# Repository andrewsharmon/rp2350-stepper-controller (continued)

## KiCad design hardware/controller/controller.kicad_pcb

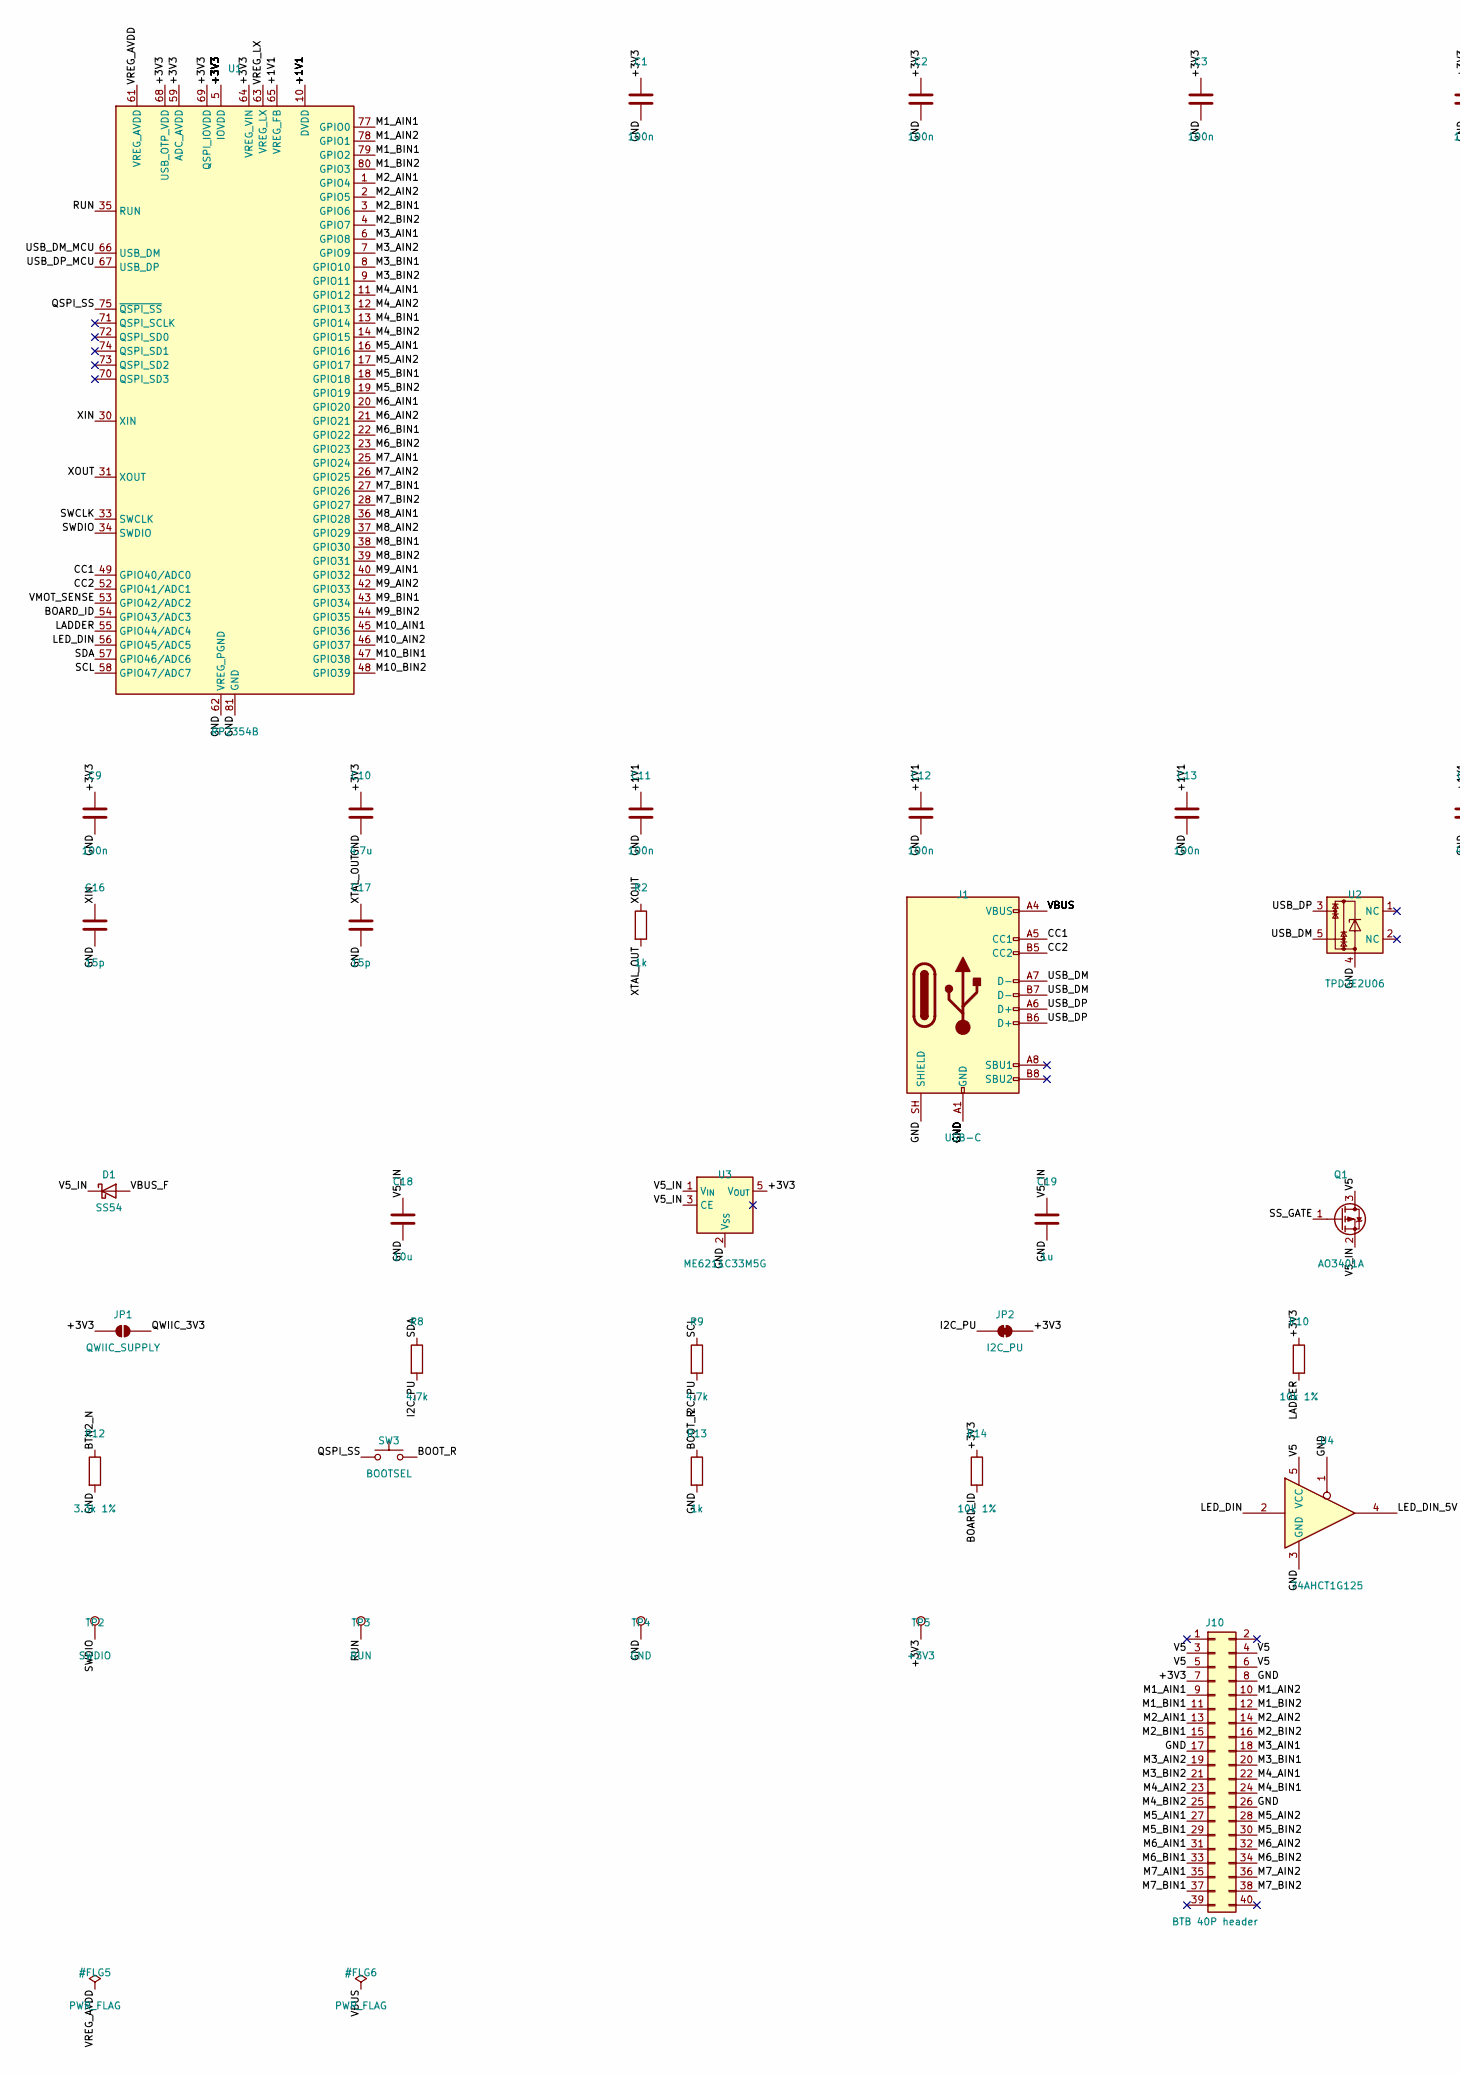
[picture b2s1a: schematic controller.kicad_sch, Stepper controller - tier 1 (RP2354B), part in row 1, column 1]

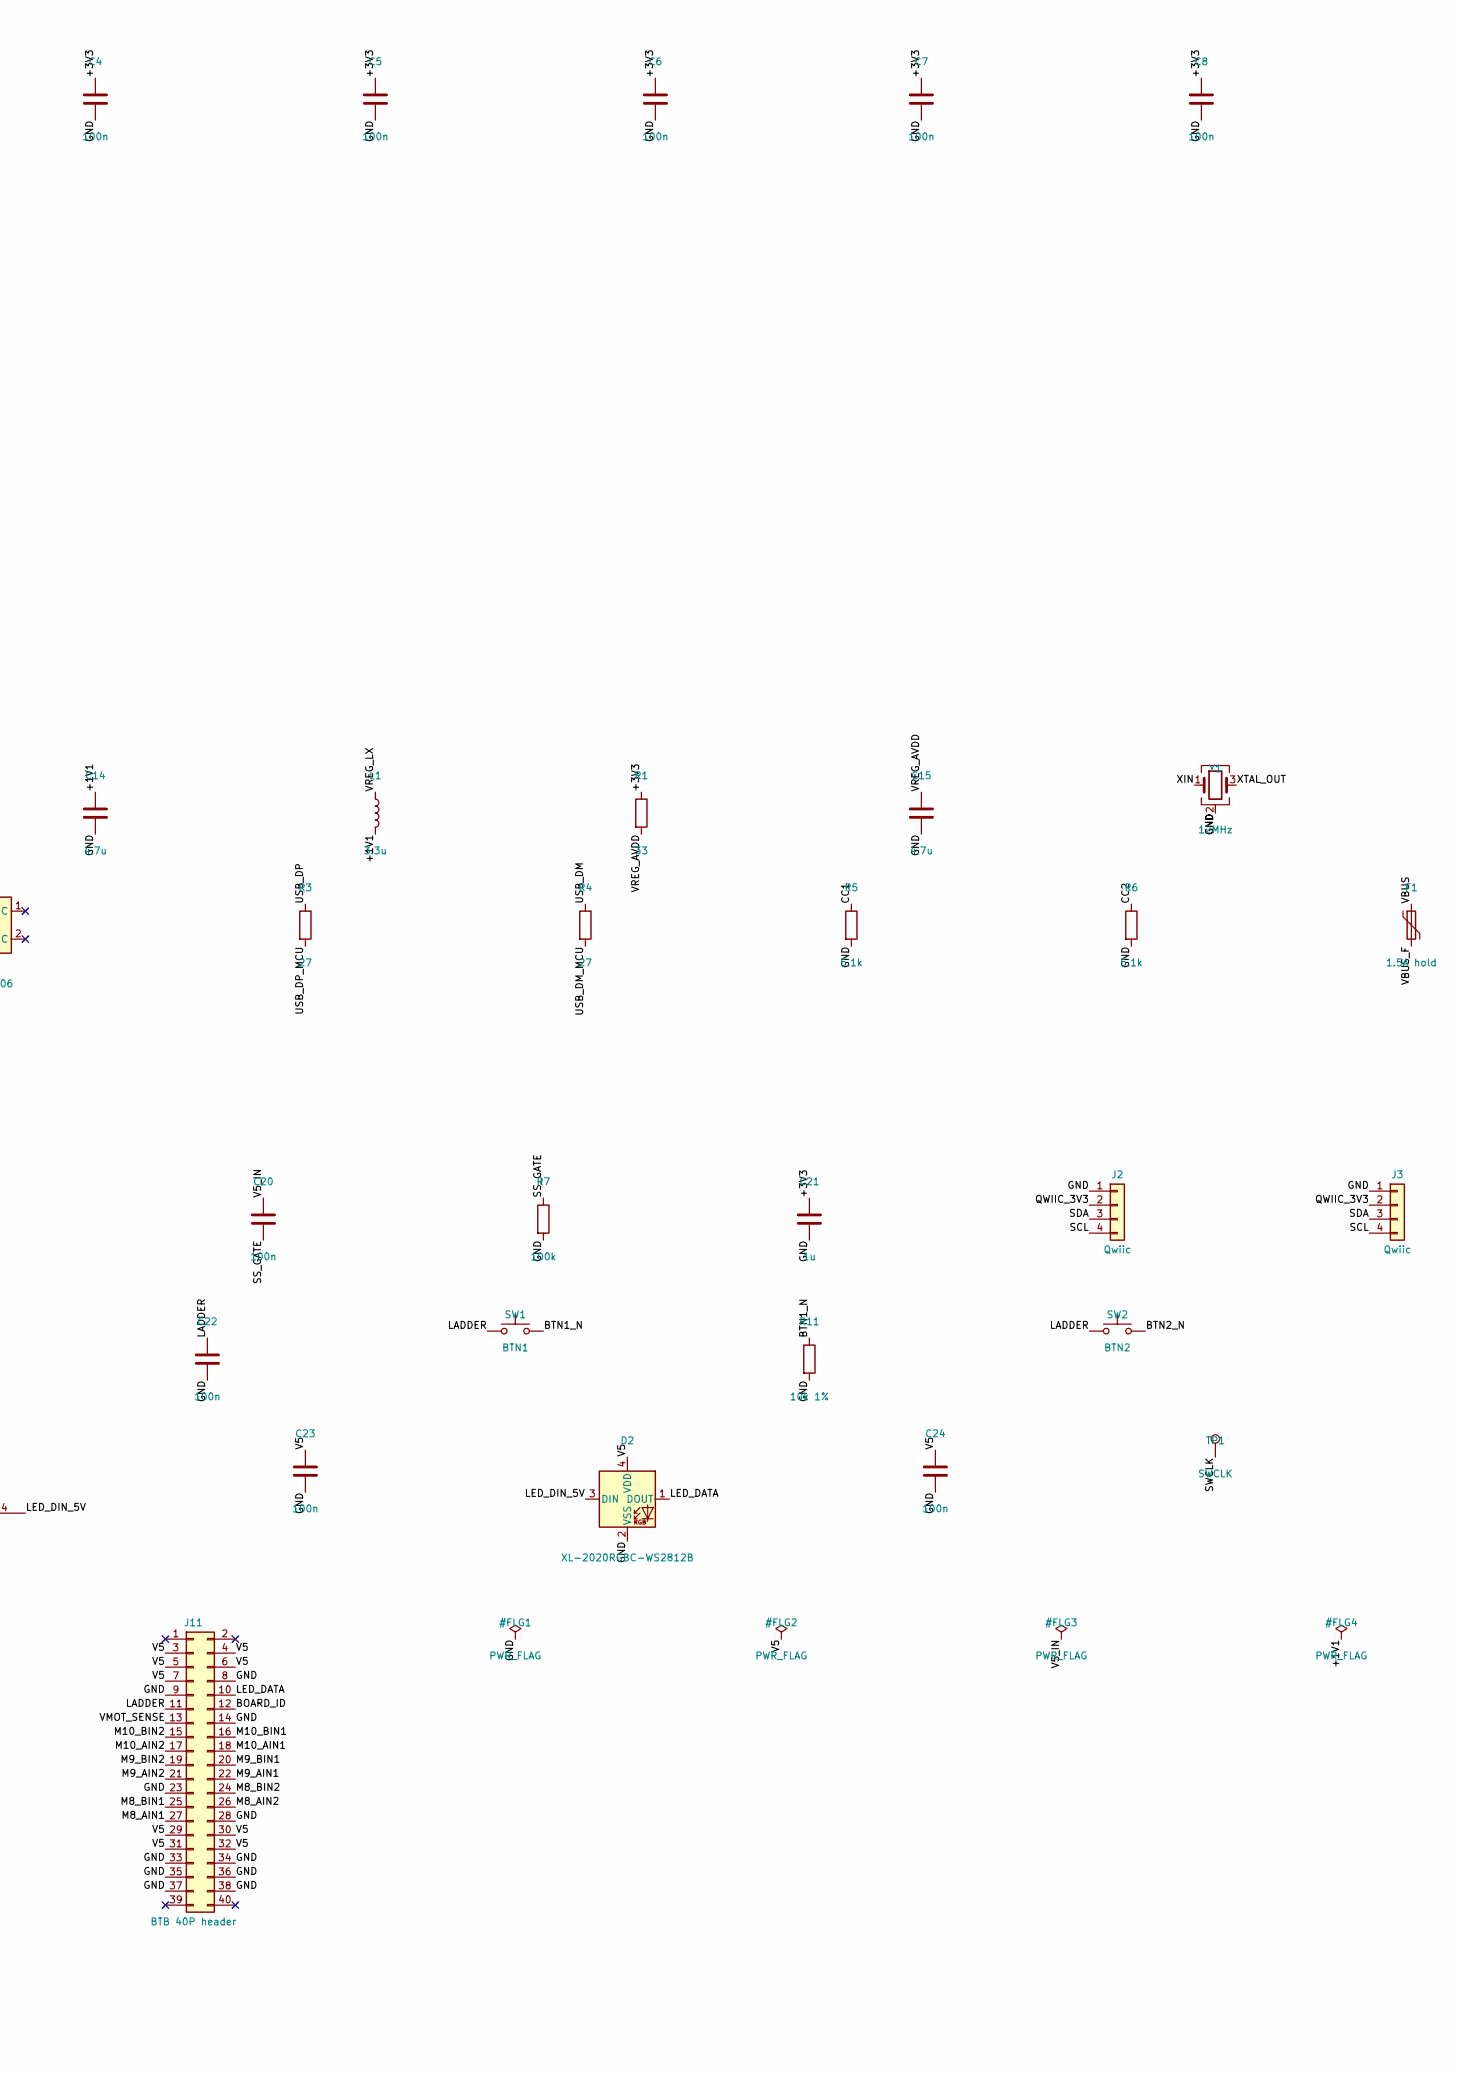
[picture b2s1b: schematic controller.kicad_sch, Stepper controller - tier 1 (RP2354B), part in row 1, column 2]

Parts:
C1, C2, C3, C4, C5, C6, C7, C8, C9, C11, C12, C13, C20, C22, C23, C24: 100n; C_0402_1005Metric; MPN CL05B104KO5NNNC; LCSC C1525
C10, C14, C15: 4.7u; C_0402_1005Metric; MPN CL05A475MP5NRNC; LCSC C23733
C16, C17: 15p; C_0402_1005Metric; MPN 0402CG150J500NT; LCSC C1548
C18: 10u; C_0805_2012Metric; MPN CL21A106KAYNNNE; LCSC C15850
C19, C21: 1u; C_0402_1005Metric; MPN CL05A105KA5NQNC; LCSC C52923
D1: SS54; D_SMA; MPN SS54; LCSC C22452
D2: XL-2020RGBC-WS2812B; LED_WS2812B-2020_PLCC4_2.0x2.0mm; MPN XL-2020RGBC-WS2812B; LCSC C5349955
F1: 1.5A hold; Fuse_1812_4532Metric; MPN SMD1812P150TF/8; LCSC C209721
J1: USB-C; USB_C_Receptacle_HRO_TYPE-C-31-M-12; MPN TYPE-C-31-M-12; LCSC C165948
J2, J3: Qwiic; JST_SH_BM04B-SRSS-TB_1x04-1MP_P1.00mm_Vertical; MPN BM04B-SRSS-TB; LCSC C160390
J10, J11: BTB 40P header; Hirose_DF40C-40DP_Header; MPN DF40C-40DP-0.4V(51); LCSC C424643
JP1: QWIIC_SUPPLY; SolderJumper-2_P1.3mm_Open_RoundedPad1.0x1.5mm
JP2: I2C_PU; SolderJumper-2_P1.3mm_Bridged_RoundedPad1.0x1.5mm
L1: 3.3u; L_Cenker_CKCS201610; MPN AOTA-B201610S3R3-101-T; LCSC C42411119
Q1: AO3401A; SOT-23; MPN AO3401A; LCSC C15127
R1: 33; R_0402_1005Metric; MPN 0402WGF330JTCE; LCSC C25105
R2, R13: 1k; R_0402_1005Metric; MPN 0402WGF1001TCE; LCSC C11702
R3, R4: 27; R_0402_1005Metric; MPN 0402WGF270JTCE; LCSC C25100
R5, R6: 5.1k; R_0402_1005Metric; MPN 0402WGF5101TCE; LCSC C25905
R7: 100k; R_0402_1005Metric; MPN 0402WGF1003TCE; LCSC C25741
R8, R9: 4.7k; R_0402_1005Metric; MPN 0402WGF4701TCE; LCSC C25900
R10, R11, R14: 10k 1%; R_0402_1005Metric; MPN 0402WGF1002TCE; LCSC C25744
R12: 3.3k 1%; R_0402_1005Metric; MPN 0402WGF3301TCE; LCSC C25890
SW1: BTN1; SW_SPST_TS-1088-xR020; MPN TS-1088-AR02016; LCSC C720477
SW2: BTN2; SW_SPST_TS-1088-xR020; MPN TS-1088-AR02016; LCSC C720477
SW3: BOOTSEL; SW_Push_1P1T_XKB_TS-1187A; MPN TS-1187A-B-A-B; LCSC C318884
TP1: SWCLK; TestPoint_Pad_D1.0mm
TP2: SWDIO; TestPoint_Pad_D1.0mm
TP3: RUN; TestPoint_Pad_D1.0mm
TP4: GND; TestPoint_Pad_D1.0mm
TP5: +3V3; TestPoint_Pad_D1.0mm
U1: RP2354B; QFN-80-1EP_10x10mm_P0.4mm_EP3.4x3.4mm; MPN RP2354B; LCSC C39843328
U2: TPD2E2U06; SOT-553; MPN TPD2E2U06DRLR; LCSC C1972959
U3: ME6211C33M5G; SOT-23-5; MPN ME6211C33M5G-N; LCSC C82942
U4: 74AHCT1G125; SOT-23-5; MPN SN74AHCT1G125DBVR; LCSC C7484
Y1: 12MHz; Crystal_SMD_3225-4Pin_3.2x2.5mm; MPN ABM8-272-T3; LCSC C20625731

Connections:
/+1V1: C11.1, C12.1, C13.1, C14.1, L1.2, U1.10 (DVDD), U1.32 (DVDD), U1.51 (DVDD), U1.65 (VREG_FB)
/+3V3: C1.1, C2.1, C3.1, C4.1, C5.1, C6.1, C7.1, C8.1, C9.1, C10.1, C21.1, J10.7, JP1.1 (A), JP2.2 (B), R1.1, R10.1, R14.1, TP5.1, U1.5 (IOVDD), U1.15 (IOVDD), U1.24 (IOVDD), U1.29 (IOVDD), U1.41 (IOVDD), U1.50 (IOVDD), U1.59 (ADC_AVDD), U1.60 (IOVDD), U1.64 (VREG_VIN), U1.68 (USB_OTP_VDD), U1.69 (QSPI_IOVDD), U1.76 (IOVDD), U3.5 (V_{OUT})
/BOARD_ID: J11.12, R14.2, U1.54 (GPIO43/ADC3)
/BOOT_R: R13.1, SW3.2
/BTN1_N: R11.1, SW1.2
/BTN2_N: R12.1, SW2.2
/CC1: J1.A5 (CC1), R5.1, U1.49 (GPIO40/ADC0)
/CC2: J1.B5 (CC2), R6.1, U1.52 (GPIO41/ADC1)
/GND: C1.2, C2.2, C3.2, C4.2, C5.2, C6.2, C7.2, C8.2, C9.2, C10.2, C11.2, C12.2, C13.2, C14.2, C15.2, C16.2, C17.2, C18.2, C19.2, C21.2, C22.2, C23.2, C24.2, D2.2 (VSS), J1.A1 (GND), J1.A12 (GND), J1.B1 (GND), J1.B12 (GND), J1.SH (SHIELD), J2.1, J3.1, J10.8, J10.17, J10.26, J11.8, J11.9, J11.14, J11.23, J11.28, J11.33, J11.34, J11.35, J11.36, J11.37, J11.38, R5.2, R6.2, R7.2, R11.2, R12.2, R13.2, TP4.1, U1.62 (VREG_PGND), U1.81 (GND), U2.4, U3.2 (V_{SS}), U4.1, U4.3 (GND), Y1.2 (G), Y1.4 (G)
/I2C_PU: JP2.1 (A), R8.2, R9.2
/LADDER: C22.1, J11.11, R10.2, SW1.1, SW2.1, U1.55 (GPIO44/ADC4)
/LED_DATA: D2.1 (DOUT), J11.10
/LED_DIN: U1.56 (GPIO45/ADC5), U4.2
/LED_DIN_5V: D2.3 (DIN), U4.4
/M1_AIN1: J10.9, U1.77 (GPIO0)
/M1_AIN2: J10.10, U1.78 (GPIO1)
/M1_BIN1: J10.11, U1.79 (GPIO2)
/M1_BIN2: J10.12, U1.80 (GPIO3)
/M2_AIN1: J10.13, U1.1 (GPIO4)
/M2_AIN2: J10.14, U1.2 (GPIO5)
/M2_BIN1: J10.15, U1.3 (GPIO6)
/M2_BIN2: J10.16, U1.4 (GPIO7)
/M3_AIN1: J10.18, U1.6 (GPIO8)
/M3_AIN2: J10.19, U1.7 (GPIO9)
/M3_BIN1: J10.20, U1.8 (GPIO10)
/M3_BIN2: J10.21, U1.9 (GPIO11)
/M4_AIN1: J10.22, U1.11 (GPIO12)
/M4_AIN2: J10.23, U1.12 (GPIO13)
/M4_BIN1: J10.24, U1.13 (GPIO14)
/M4_BIN2: J10.25, U1.14 (GPIO15)
/M5_AIN1: J10.27, U1.16 (GPIO16)
/M5_AIN2: J10.28, U1.17 (GPIO17)
/M5_BIN1: J10.29, U1.18 (GPIO18)
/M5_BIN2: J10.30, U1.19 (GPIO19)
/M6_AIN1: J10.31, U1.20 (GPIO20)
/M6_AIN2: J10.32, U1.21 (GPIO21)
/M6_BIN1: J10.33, U1.22 (GPIO22)
/M6_BIN2: J10.34, U1.23 (GPIO23)
/M7_AIN1: J10.35, U1.25 (GPIO24)
/M7_AIN2: J10.36, U1.26 (GPIO25)
/M7_BIN1: J10.37, U1.27 (GPIO26)
/M7_BIN2: J10.38, U1.28 (GPIO27)
/M8_AIN1: J11.27, U1.36 (GPIO28)
/M8_AIN2: J11.26, U1.37 (GPIO29)
/M8_BIN1: J11.25, U1.38 (GPIO30)
/M8_BIN2: J11.24, U1.39 (GPIO31)
/M9_AIN1: J11.22, U1.40 (GPIO32)
/M9_AIN2: J11.21, U1.42 (GPIO33)
/M9_BIN1: J11.20, U1.43 (GPIO34)
/M9_BIN2: J11.19, U1.44 (GPIO35)
/M10_AIN1: J11.18, U1.45 (GPIO36)
/M10_AIN2: J11.17, U1.46 (GPIO37)
/M10_BIN1: J11.16, U1.47 (GPIO38)
/M10_BIN2: J11.15, U1.48 (GPIO39)
/QSPI_SS: SW3.1, U1.75 (~QSPI_SS)
/QWIIC_3V3: J2.2, J3.2, JP1.2 (B)
/RUN: TP3.1, U1.35 (RUN)
/SCL: J2.4, J3.4, R9.1, U1.58 (GPIO47/ADC7)
/SDA: J2.3, J3.3, R8.1, U1.57 (GPIO46/ADC6)
/SS_GATE: C20.2, Q1.1 (G), R7.1
/SWCLK: TP1.1, U1.33 (SWCLK)
/SWDIO: TP2.1, U1.34 (SWDIO)
/USB_DM: J1.A7 (D-), J1.B7 (D-), R4.1, U2.5
/USB_DM_MCU: R4.2, U1.66 (USB_DM)
/USB_DP: J1.A6 (D+), J1.B6 (D+), R3.1, U2.3
/USB_DP_MCU: R3.2, U1.67 (USB_DP)
/V5: C23.1, C24.1, D2.4 (VDD), J10.3, J10.4, J10.5, J10.6, J11.3, J11.4, J11.5, J11.6, J11.7, J11.29, J11.30, J11.31, J11.32, Q1.3 (D), U4.5 (VCC)
/V5_IN: C18.1, C19.1, C20.1, D1.1 (K), Q1.2 (S), U3.1 (V_{IN}), U3.3 (CE)
/VBUS: F1.1, J1.A4 (VBUS), J1.A9 (VBUS), J1.B4 (VBUS), J1.B9 (VBUS)
/VBUS_F: D1.2 (A), F1.2
/VMOT_SENSE: J11.13, U1.53 (GPIO42/ADC2)
/VREG_AVDD: C15.1, R1.2, U1.61 (VREG_AVDD)
/VREG_LX: L1.1, U1.63 (VREG_LX)
/XIN: C16.1, U1.30 (XIN), Y1.1
/XOUT: R2.1, U1.31 (XOUT)
/XTAL_OUT: C17.1, R2.2, Y1.3

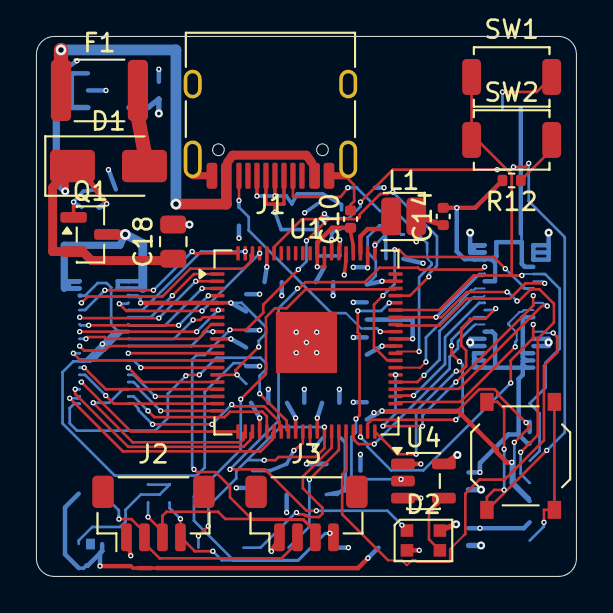
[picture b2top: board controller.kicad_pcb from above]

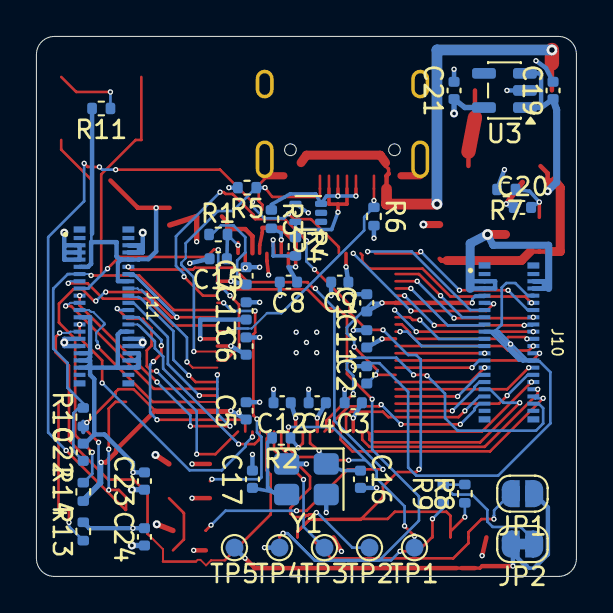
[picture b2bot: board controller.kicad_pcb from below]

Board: 4 copper layers, 30.0 x 30.0 mm, 63 parts (46 on the bottom side), 76 nets.

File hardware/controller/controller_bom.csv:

"Refs","Value","Footprint","Qty","MPN","LCSC","Note"
"C1,C2,C3,C4,C5,C6,C7,C8,C9,C11,C12,C13,C22,C23,C24","100n","Capacitor_SMD:C_0402_1005Metric","15","CL05B104KO5NNNC","C1525",""
"C10,C14,C15","4.7u","Capacitor_SMD:C_0402_1005Metric","3","CL05A475MP5NRNC","C23733",""
"C16,C17","15p","Capacitor_SMD:C_0402_1005Metric","2","0402CG150J500NT","C1548",""
"C18","10u","Capacitor_SMD:C_0805_2012Metric","1","CL21A106KAYNNNE","C15850",""
"C19,C21","1u","Capacitor_SMD:C_0402_1005Metric","2","CL05A105KA5NQNC","C52923",""
"C20","100n","Capacitor_SMD:C_0402_1005Metric","1","CL05B104KO5NNNC","C1525","soft-start timing with the 100k"
"D1","SS54","Diode_SMD:D_SMA","1","SS54","C22452","MDD; Vf 0.55 V @ 5 A"
"D2","XL-2020RGBC-WS2812B","LED_SMD:LED_WS2812B-2020_PLCC4_2.0x2.0mm","1","XL-2020RGBC-WS2812B","C5349955","XINGLIGHT; WS2812B-2020 pinout and footprint; Worldsemi C965555 was out of stock at JLCPCB"
"F1","1.5A hold","Fuse:Fuse_1812_4532Metric","1","SMD1812P150TF/8","C209721","PTTC; 1.5 A hold / 3 A trip, 8 V; alt C21002"
"J1","USB-C","Connector_USB:USB_C_Receptacle_HRO_TYPE-C-31-M-12","1","TYPE-C-31-M-12","C165948","THT shell legs; enclosure supports receptacle"
"J2,J3","Qwiic","Connector_JST:JST_SH_BM04B-SRSS-TB_1x04-1MP_P1.00mm_Vertical","2","BM04B-SRSS-TB","C160390",""
"J10","BTB 40P header","stack:Hirose_DF40C-40DP_Header","1","DF40C-40DP-0.4V(51)","C424643","connector A, board underside"
"J11","BTB 40P header","stack:Hirose_DF40C-40DP_Header","1","DF40C-40DP-0.4V(51)","C424643","connector B, board underside; offset placement keys stack"
"L1","3.3u","Inductor_SMD:L_Cenker_CKCS201610","1","AOTA-B201610S3R3-101-T","C42411119","Abracon part per RP2350 design guide; 2016 size"
"Q1","AO3401A","Package_TO_SOT_SMD:SOT-23","1","AO3401A","C15127","AOS; 60 mohm @ 4.5 V, Vth ~0.9 V"
"R1","33","Resistor_SMD:R_0402_1005Metric","1","0402WGF330JTCE","C25105",""
"R2,R13","1k","Resistor_SMD:R_0402_1005Metric","2","0402WGF1001TCE","C11702",""
"R3,R4","27","Resistor_SMD:R_0402_1005Metric","2","0402WGF270JTCE","C25100",""
"R5,R6","5.1k","Resistor_SMD:R_0402_1005Metric","2","0402WGF5101TCE","C25905",""
"R7","100k","Resistor_SMD:R_0402_1005Metric","1","0402WGF1003TCE","C25741","soft-start timing with the 100n"
"R8,R9","4.7k","Resistor_SMD:R_0402_1005Metric","2","0402WGF4701TCE","C25900",""
"R10,R11,R14","10k 1%","Resistor_SMD:R_0402_1005Metric","3","0402WGF1002TCE","C25744",""
"R12","3.3k 1%","Resistor_SMD:R_0402_1005Metric","1","0402WGF3301TCE","C25890",""
"SW1","BTN1","Button_Switch_SMD:SW_SPST_TS-1088-xR020","1","TS-1088-AR02016","C720477","XUNPU 3.9x3.0 mm 2-pad; small so the BTB fan-out routes"
"SW2","BTN2","Button_Switch_SMD:SW_SPST_TS-1088-xR020","1","TS-1088-AR02016","C720477","XUNPU 3.9x3.0 mm 2-pad; small so the BTB fan-out routes"
"SW3","BOOTSEL","Button_Switch_SMD:SW_Push_1P1T_XKB_TS-1187A","1","TS-1187A-B-A-B","C318884",""
"U1","RP2354B","Package_DFN_QFN:QFN-80-1EP_10x10mm_P0.4mm_EP3.4x3.4mm","1","RP2354B","C39843328","2 MB in-package flash; leave QSPI_SD0-3/SCLK unconnected"
"U2","TPD2E2U06","Package_TO_SOT_SMD:SOT-553","1","TPD2E2U06DRLR","C1972959","TI; 1.5 pF; pins 1-2 NC"
"U3","ME6211C33M5G","Package_TO_SOT_SMD:SOT-23-5","1","ME6211C33M5G-N","C82942",""
"U4","74AHCT1G125","Package_TO_SOT_SMD:SOT-23-5","1","SN74AHCT1G125DBVR","C7484",""
"Y1","12MHz","Crystal:Crystal_SMD_3225-4Pin_3.2x2.5mm","1","ABM8-272-T3","C20625731","Abracon, per RP2350 design guide; other crystals need retuning and testing"

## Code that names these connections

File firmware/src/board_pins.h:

#pragma once

// Application pin map. Motors always sit on GPIO 4*n..4*n+3; boards with
// fewer GPIOs run the remaining motors without pins.

#include "pico.h"

#define ADC_NONE 0xffu

#if NUM_BANK0_GPIOS > 32
// RP2354B stepper controller (hardware/README.md).
#define BOARD_MOTORS_WITH_PINS 10
#define BOARD_CC1_GPIO        40
#define BOARD_CC2_GPIO        41
#define BOARD_VMOT_GPIO       42
#ifdef BOARD_SINGLE_SH_PROTO
#define BOARD_VMOT_RATIO      4.9f   // 39k / 10k divider
#else
#define BOARD_VMOT_RATIO      5.0f   // 1:5 divider
#endif
#define BOARD_ID_GPIO         43
#define BOARD_LADDER_GPIO     44
#define BOARD_WS2812_GPIO     45
// Qwiic: I2C1 target (hardware/README.md). External pull-ups (RP2350-E9).
#define BOARD_I2C_SDA_GPIO    46
#define BOARD_I2C_SCL_GPIO    47
#define BOARD_I2C_TARGET_ADDR 0x42
#ifdef BOARD_SINGLE_SH_PROTO
// Axes in row order along the motor connectors, from the far end to the
// USB end: J13 M5 M6, J14 M7 M8, J15 M9 M10, J11 M1 M2, J12 M3 M4. The ToF
// map (tof_overlay.c) and the built-in programs (player.c) lay the axes
// out in this order.
#define BOARD_AXIS_ROW {4, 5, 6, 7, 8, 9, 0, 1, 2, 3}
#endif
#else
// Pico 2 bench (RP2350A, GPIO 0-29). Motors 1-5 on GPIO 0-19. The ladder and
// board ID go on the ADC header pins; VSYS/3 stands in for VMOTOR_SENSE.
// No free pins for the I2C target, so it is compiled out.
#define BOARD_MOTORS_WITH_PINS 5
#define BOARD_CC1_GPIO        ADC_NONE
#define BOARD_CC2_GPIO        ADC_NONE
#define BOARD_VMOT_GPIO       29
#define BOARD_VMOT_RATIO      3.0f   // Pico 2 VSYS/3 divider
#define BOARD_ID_GPIO         28
#define BOARD_LADDER_GPIO     26
#define BOARD_WS2812_GPIO     20
#endif

// Place of `axis` (0-based) along the row of actuators, counting only axes
// below `n`: its position in BOARD_AXIS_ROW, or the axis itself without one.
static inline int board_row_slot(int axis, int n) {
#ifdef BOARD_AXIS_ROW
    static const unsigned char row[] = BOARD_AXIS_ROW;
    int slot = 0;
    for (unsigned k = 0; k < sizeof row; k++) {
        if (row[k] == axis)
            return slot;
        if (row[k] < n)
            slot++;
    }
#else
    (void)n;
#endif
    return axis;
}
